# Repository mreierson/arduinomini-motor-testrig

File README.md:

## Arduino Mini / Pololu motor driver + potentiometer

Arduino with pot. input to control speed wheel for testing encoders

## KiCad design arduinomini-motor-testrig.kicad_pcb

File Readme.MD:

## Arduino Mini / Pololu motor driver + potentiometer

Arduino with pot. input to control speed wheel for testing encoders

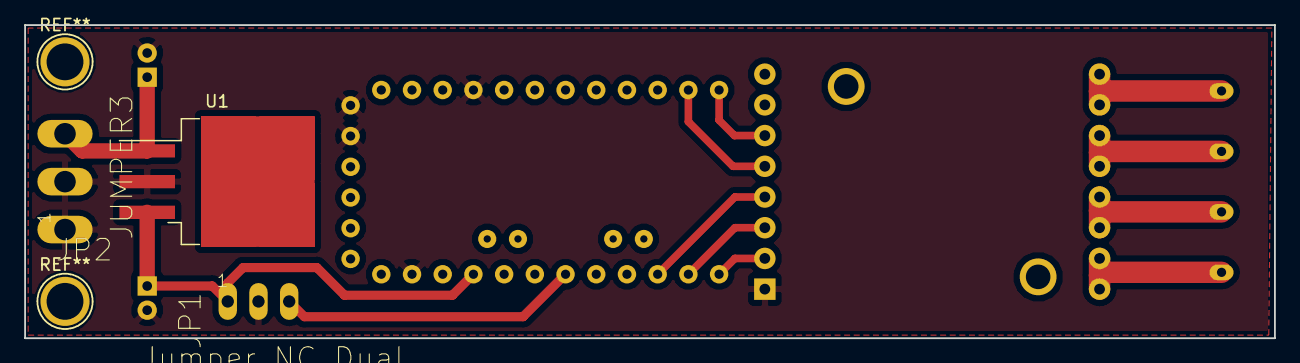
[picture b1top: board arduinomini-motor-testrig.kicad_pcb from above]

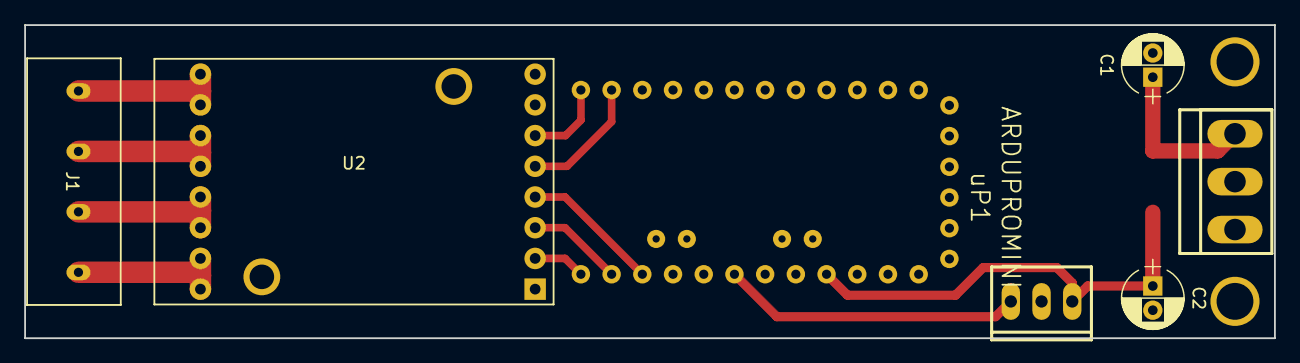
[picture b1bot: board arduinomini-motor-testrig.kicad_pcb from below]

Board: 2 copper layers, 103.4 x 25.9 mm, 8 parts (7 on the bottom side), 13 nets.

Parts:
C1, C2: CP; CP_Radial_D5.0mm_P2.00mm
J1: Conn_01x04_Female; WJ301_4P
JP1: Jumper_NC_Dual; con-hdrs40-MTA-100-3V
JP2: JUMPER3; con-amp-MTA-156-3V
U1: LM7805_TO220; TO-263-3_TabPin2
U2: DRIVER_18V15
uP1: ARDUPROMINI; ArduProMini

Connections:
+5V: C2.1, JP1.1, U1.3, uP1.22
+12V: C1.1, JP2.3, U1.1
GND: C1.2, C2.2, JP1.2, JP2.1, JP2.2, U1.2, U2.8, uP1.1, uP1.2, uP1.10, uP1.20
unnamed: J1.1, U2.9
unnamed: J1.2, U2.10
unnamed: J1.3, U2.11
unnamed: J1.4, U2.12
unnamed: JP1.3, uP1.25
unnamed: U2.3, uP1.18
unnamed: U2.4, uP1.17
unnamed: U2.5, uP1.28
unnamed: U2.6, uP1.29
unnamed: U2.7, uP1.30

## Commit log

2018-09-05 Update to KiCad 5
